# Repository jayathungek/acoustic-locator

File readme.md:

Table of Contents
=================

   * [acoustic-locator](#acoustic-locator)
      * [Hardware setup](#hardware-setup)
        * [The Microphone Circuit](#the-microphone-circuit)
        * [The Humidity/Temperature Sensor](#the-humiditytemperature-sensor)
        * [The Laser LED circuit](#the-laser-led-circuit)
        * [The Servo Circuit](#the-servo-circuit)
        * [Mechanical Design](#mechanical-design)
      * [Prerequisites](#prerequisites)
      * [Installation](#installation)
      * [How to use](#how-to-use)
      
# acoustic-locator

## Hardware setup

The acoustic locator hardware consists of two basic modules. The first module is the microphone module build on a PCB board that enables the placement of three MEMS microphones. The second module is the positioning module which consists basically of two servo motors, one being responsible for the horizontal movement of the mechanism and the other for the vertical. The front and back views of the acoustic locator are shown in figure 1. The sound source direction detection is achieved with the use of three microphones forming an equilateral triangle. The three holes at the edges of the acoustic locator identified on the front view are the openings for the three microphones. The opening in the middle of the acoustic locator, shown in the front view is the opening for the laser diode. The back view shows the positioning mechanism with the two servo motors.

                            Figure 1
                            
 The PCB board for the microphones is shown in figure 2. An IDC connector is used to connect the board with the Raspberry Pi board. The microphones used are Integrated Inter-IC Sound Bus (I2S) compatible digital MEMS microphones. I2S is a serial bus standard/protocol that enable the interface of one or two microphones on a microcontroller through a serial connection. Since the acoustic locator uses three microphones, a multiplexer is used to enable the connection of the microphones on the I2S bus. 

The microphones board also contains the circuit for the humidity/temperature sensor. The reason for using this sensor is because the speed of sound can vary with the temperature and the humidity. If the acoustic locator is used in normal room conditions then there is no need for the temperature/humidity sensor. If the acoustic locator is going to be used in places with extreme temperatures or humidity then the values of the temperature and humidity can be used to calculate the speed of sound and adjust the operation of the acoustic locator accordingly. 

The third module on the microphones PCB board is a laser LED circuit consisting of a LED driver and the laser LED. The laser LED is used for testing purposes, in order to identify the direction at which the acoustic locator is pointing to. On the final product, the laser LED can be replaced by a web camera, so that the camera will point to the person speaking, as explained in the introduction of this report.

                            Figure 2
                            
### The Microphone Circuit

The microphones used by the acoustic locator are the ICS-43432 digital I2S microphones from InvenSence. The ICS-43432 microphone includes all the required circuitry so that it can be interfaced directly with a microcontroller or a DSP, without the use of an audio codec. As shown in figure 3 the ICS-43432 contains in the same package the MEMS sensor with the signal conditioning circuit, the A/D converter, the anti-aliasing filter and a 24-bit I2S interface. The data sheet, handling information and application notes for the ICS-43432 microphone can be found [here]( https://www.invensense.com/products/digital/ics-43432/).

The ‘Config’ input is used in cases where it is required to modify the internal registers of the device. For normal operation, the ‘Config’ signal must be connected to the ground.  The ‘Left/Right’ (LR) channel select signal is used to specify to which one of the two I2S channels is the microphone connected to. If the L/R pin is connected to the ground (or set to Low), the microphone outputs its signal to the left channel of the I2C frame. If the L/R pin is connected to the supply voltage (or set to High), the microphone outputs its signal to the right channel of the I2C frame.

The I2C signals are the ‘SCK’ (Serial Data Clock for the I2S interface) input signal, the ‘SD’ (Serial Data Output for the I2S interface) signal and the ‘WS’ (Serial Data Word Select for the I2S interface) input signal. If the ‘WS’ signal is set Low, the left microphone sends its data on the ‘SD’ signal, otherwise the right microphone sends its data. The ‘SD’ line must be pull down to the ground using a 100K resistor. A typical circuit with two microphones connected to a DSP or a microcontroller is shown in figure 4.

                              Figure 3

                              Figure 4
                              
The circuit diagram of the acoustic locator microphone board is shown in figure 5. Because the acoustic locator uses three microphones and the I2S interface supports only two, a demultiplexer is used to allow two microphone to share the same I2S channel. The demultiplexer used is the TS3A24159 dual 2-channel SPDT bidirectional analogue switch. As shown in the circuit diagram, the select input (In1) of the analogue switch is connected to the GPIO9 signal of the Raspberry Pi, while the Com input is connected to the WS signal (signal GPIO19).

Setting the In1 pin to low, the WS signal is switched to the WS signal of the Mic1 microphone, thus reading the data from Mic1.  Setting the In1 pin to high, the WS signal is switched to the WS signal of the Mic2 microphone, thus reading the data from Mic2. Since the LR inputs for Mic1 and Mic2 are connected to the supply voltage, both microphones are treated as Right channel microphones. The LS signal of microphone Mic3 is connected to the ground, therefore, this microphone is treated as the Left channel microphone.

                              Figure 5

### The Humidity/Temperature Sensor

The Humidity/Temperature Sensor used by the acoustic locator is the HIH6030-021-001 digital I2C humidity/temperature from Honeywell. This device combines a humidity and a temperature sensor in the same package. The data sheet, handling information and application notes for the HIH6030-021-001 digital I2C humidity/temperature can be found [here](https://sensing.honeywell.com/HIH6030-021-001-humidity-sensors). 

The pinout with the typical application circuit diagram, given in the device datasheet is shown in figure 13.The same circuit is used  by the acoustic locator as shown in the circuit diagram in figure 5.The SCL pin is connected to the I2C clock, while the SDA pin is connected to the I2C data line. Both the SCL and the SDA pins must be pulled up with a 2.2K resistor each. The supply pin must be decoupled with a 0.1µF capacitor, while the Vcore pin must be connected to the ground through a 0.22µF capacitor. The AL_L (Alarm Low) and the AL_H (Alarm High) pins are used in the case an external device such as a relay or a LED are needed to be controlled directly by the sensor.

                                Figure 6
                                                           
### The Laser LED circuit

The laser LED circuit, shown in figure 7, consists of the laser diode, MOSFET transistor driver and resistor. The transistor driver is used because the Raspberry Pi cannot provide the amount of current required to operate the laser LED. The resistor is used to limit the current through the laser to the value lower than the maximum LED current. The operation of the laser is achieved by controlling the state of the GPIO6 of the Raspberry Pi.

                                Figure 7
                                
### The Servo Circuit

The movement of the positioning mechanism is achieved by the use of two servo motors. These motors are connected by the Raspberry Pi, through a board that is attached on the Raspberry Pi as a shield shown in figure 8. This shield also provides a connection from the Raspberry Pi to the microphones board through an IDC connector and a ribbon cable.The circuit diagram for the connection of the two servo motors to the Raspberry Pi is shown in figure 9. The speed and direction of rotation of the servo motors is achieved through the PWM signals obtained from the GPIO12 and the GPIO13 signals of the Raspberry Pi.

                                Figure 8

                                Figure 9
                                
### Mechanical Design

The mechanical design consists of the direction mechanism. This design features three parts: (a) the base, (b) a gimbal and (c) the head.

The base serves two functions: it supports the device as well as houses the Raspberry Pi, along with the locator interface board. The design allows the Raspberry Pi to be connected to a PC/laptop without opening the base.
The pan/tilt gimbal aids the movement of the device. It is capable of 180° rotation around the vertical axis as well as 100° up and down. The gimbal is mounts on top of the base as well as holding the head.

The head – a 3D printed part – clicks in place on top of the gimbal. The part is designed to secure the microphones in their respective places. The PCB just slides intro the head, thus no screws are required to hold the electronics on the gimbal.

## Prerequisites
The following steps are needed to configure the raspberry pi for I2S microphone support:

1. Enable I2S communication:- 
  ```
  $ sudo nano /boot/config.txt
  ```
  1.1 Navigate the file and uncomment the the line that contains `#dtparam=i2s=on`. 
  
2. Add the reference for the chip on the Raspberry Pi 3 that handles the I2S into the modules file:- 
  ```
  $ sudo nano  /etc/modules
  ``` 
  2.1 Add the line `snd-bcm2835` to this file.
  
3. Reboot:- 
  ```
  $ sudo reboot
  ```
  
4. Run this command and verify that it outputs `snd_soc_bcm2835_i2s`:-
  ```
  $ lsmod | grep snd
  ```
  
5. Install dependancies and set permissions:- 
  ```
  $ sudo apt-get -y install bc libncurses5-dev
  $ sudo wget https://raw.githubusercontent.com/notro/rpi-source/master/rpi-source -O /usr/bin/rpi-source`
  $ sudo chmod +x /usr/bin/rpi-source
  ```
6. Update `rpi-source` and run:-
  ```
  $ /usr/bin/rpi-source -q --tag-update`
  $ rpi-source
  ```
  
7. Mount the developent system debugger:-
  ```$ sudo mount -t debugfs debugs /sys/kernel/debug```
  
8. Check for the presence of the 3f203000.i2s module:-
  ```$ sudo cat /sys/kernel/debug/asoc/platforms```
  
9. Download Paul Creaser's I2S audio module, navigate to it and build it:-
  ```
  $ git clone https://github.com/PaulCreaser/rpi-i2s-audio
  $ cd rpi-i2s-audio
  $ make -C /lib/modules/$(uname -r )/build M=$(pwd) modules
  ```
  
10. Insert this module and verify its presence:-
  ```
  $ sudo insmod my_loader.ko
  $ lsmod | grep my_loader
  $ dmesg | tail
  ```
  
11. To load the module every time the pi is booted up:-
  ```
  $ sudo cp my_loader.ko /lib/modules/$(uname -r)
  $ echo 'my_loader' | sudo tee --append /etc/modules > /dev/null
  $ sudo depmod -a
  $ sudo modprobe my_loader
  ```

## Installation
1. Clone this repository: `$ git clone git@github.com:jayathungek/acoustic-locator.git`
2. Navigate to the main directory: `$ cd acoustic-locator`
3. Run tests: `$ make runtests`. All the tests should pass.
4. Build: `$ make`

A binary called `locator` is generated in the current working directory. Running this with `$ sudo ./locator` will start the main loop of the program and the gimbals will move in response to loud noises. Alternatively, f you wish to run `locator` on boot, edit `/etc/rc.local` so that it contains the path to the binary:
   ```
   #!/bin/sh -e
   #
   # rc.local
   #
   # This script is executed at the end of each multiuser runlevel.
   # Make sure that the script will "exit 0" on success or any other
   # value on error. 
   #
   # In order to enable or disable this script just change the execution
   # bits.
   #
   # By default this script does nothing.

   sudo /home/pi/acoustic-locator/locator &

   exit 0
   ```

## How to use
The raspberry pi is powered by a 5V micro usb cable and is perfectly capable of driving the servo motors from its 5V pins. Assuming all the steps above have been followed, simply plugging in the device to any 5V DC supply will start the location program.

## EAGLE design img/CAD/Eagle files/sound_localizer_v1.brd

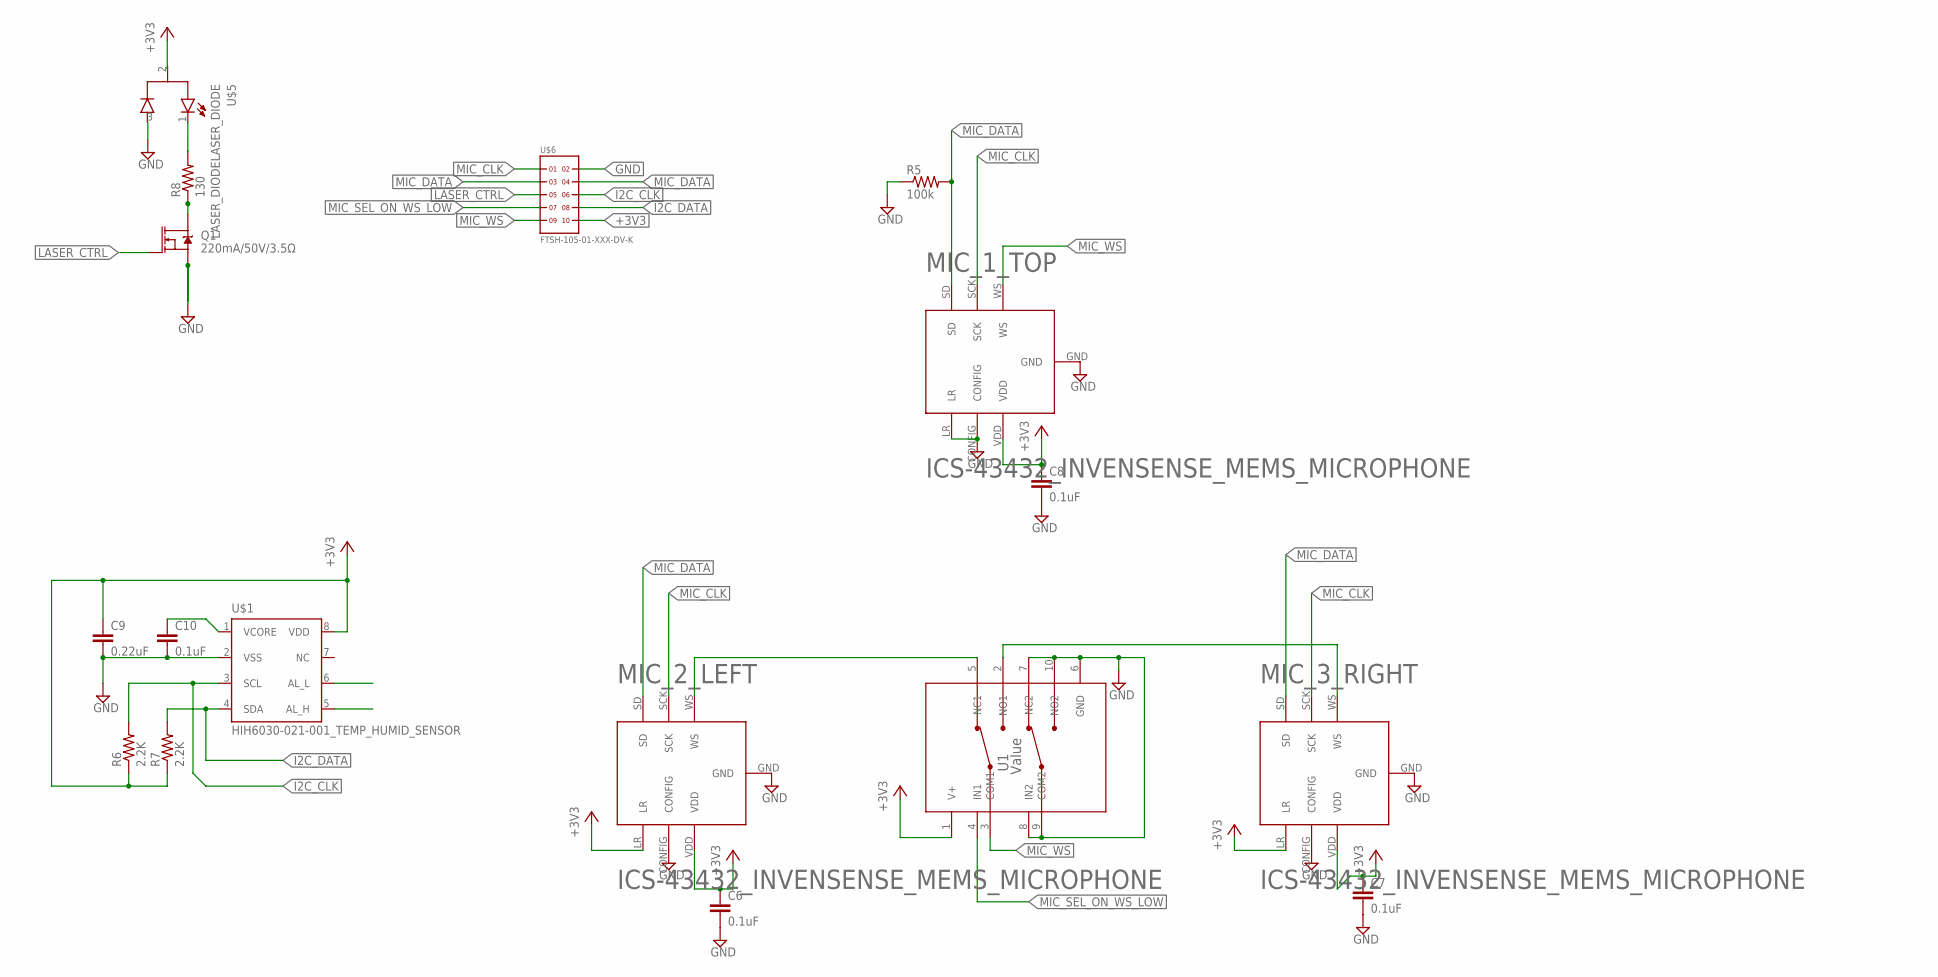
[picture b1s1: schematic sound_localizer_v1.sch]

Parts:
C6, C7, C8, C10: 0.1uF; C0805K
C9: 0.22uF; C0805K
MIC_1_TOP, MIC_2_LEFT, MIC_3_RIGHT: ICS-43432_INVENSENSE_MEMS_MICROPHONE; MEMS_MIC
Q1: 220mA/50V/3.5Ω; SOT23-3
R5: 100k; M0805
R6, R7: 2.2K; M0805
R8: 130; M0805
U1: Value; DGS0010A_N
U$1: HIH6030-021-001_TEMP_HUMID_SENSOR; SOIC8
U$5: LASER_DIODELASER_DIODE; TO46-LX
U$6: FTSH-105-01-XXX-DV-K

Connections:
+3V3: C6.1, C7.1, C8.1, C9.1, MIC_1_TOP.VDD, MIC_2_LEFT.LR, MIC_2_LEFT.VDD, MIC_3_RIGHT.LR, MIC_3_RIGHT.VDD, R6.1, R7.1, U1.1 (V+), U$1.8 (VDD), U$5.2, U$6.10
GND: C6.2, C7.2, C8.2, C9.2, C10.2, MIC_1_TOP.CONFIG, MIC_1_TOP.GND, MIC_1_TOP.LR, MIC_2_LEFT.CONFIG, MIC_2_LEFT.GND, MIC_3_RIGHT.CONFIG, MIC_3_RIGHT.GND, Q1.2 (S), R5.1, U1.6 (GND), U1.7 (NC2), U1.8 (IN2), U1.9 (COM2), U1.10 (NO2), U$1.2 (VSS), U$6.2
I2C_CLK: R6.2, U$1.3 (SCL), U$6.6
I2C_DATA: R7.2, U$1.4 (SDA), U$6.8
LASER_CTRL: Q1.1 (G), U$6.5
LED_CATHODE: R8.2, U$5.1
MIC_CLK: MIC_1_TOP.SCK, MIC_2_LEFT.SCK, MIC_3_RIGHT.SCK, U$6.1
MIC_DATA: MIC_1_TOP.SD, MIC_2_LEFT.SD, MIC_3_RIGHT.SD, R5.2, U$6.3, U$6.4
MIC_SEL_ON_WS_LOW: U1.4 (IN1), U$6.7
MIC_WS: MIC_1_TOP.WS, U1.3 (COM1), U$6.9
unnamed: MIC_2_LEFT.WS, U1.5 (NC1)
unnamed: MIC_3_RIGHT.WS, U1.2 (NO1)
unnamed: C10.1, U$1.1 (VCORE)
unnamed: Q1.3 (D), R8.1
NC: U$1.6 (AL_L)
P$1: U$5.3

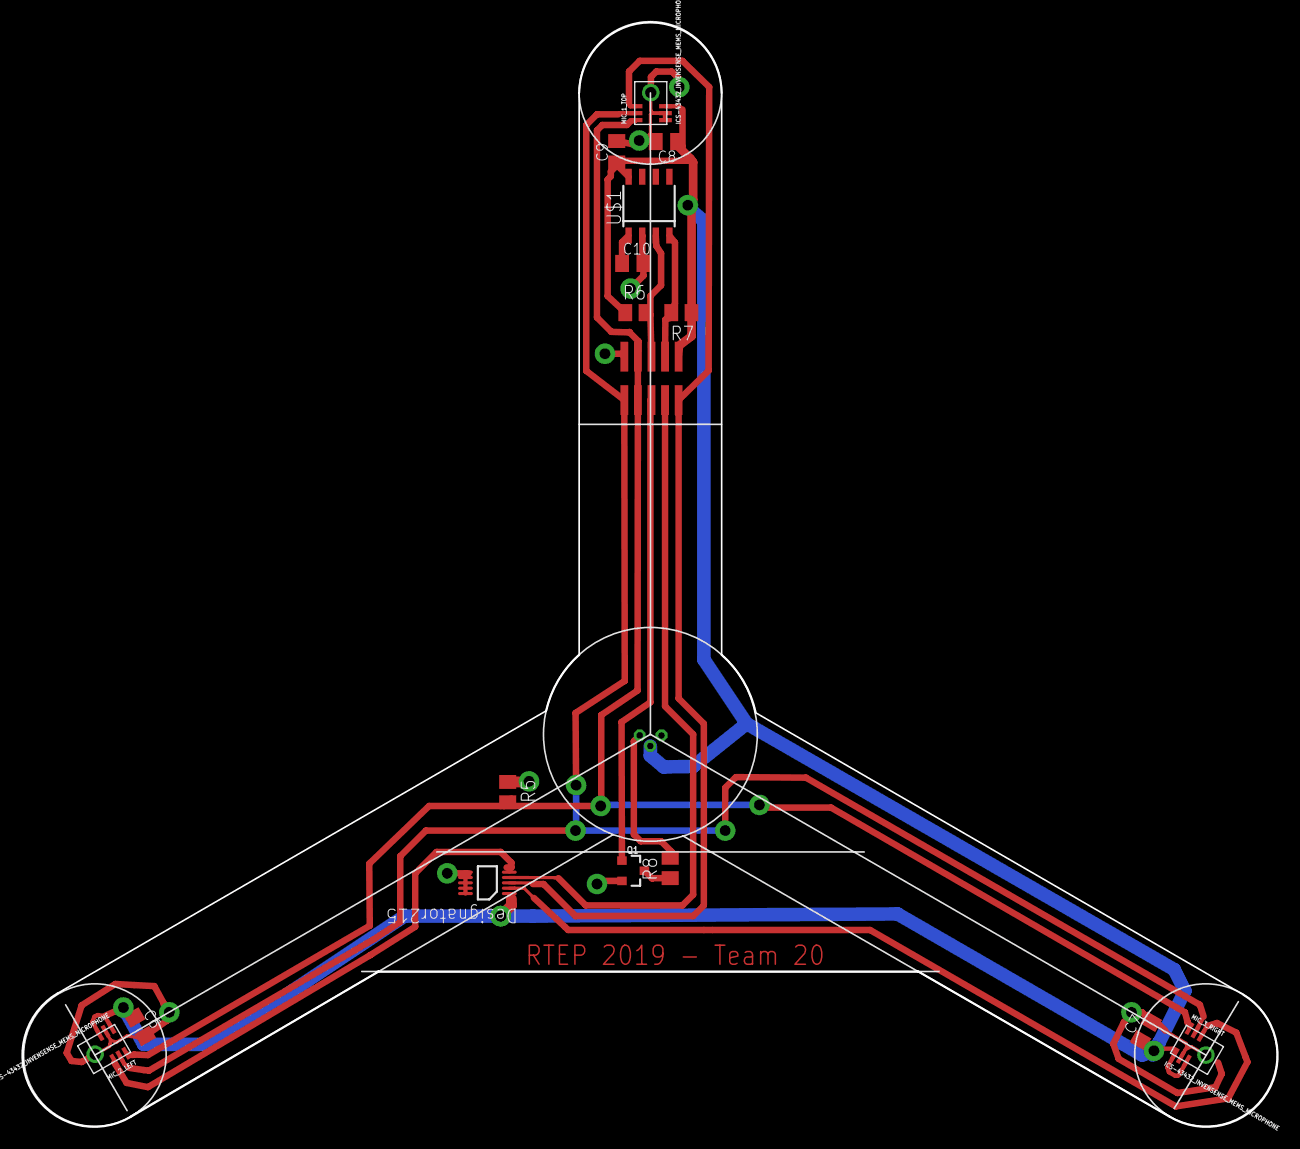
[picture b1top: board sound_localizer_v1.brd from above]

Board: 2 copper layers, 117.4 x 103.3 mm, 17 parts (1 on the bottom side), 14 nets.

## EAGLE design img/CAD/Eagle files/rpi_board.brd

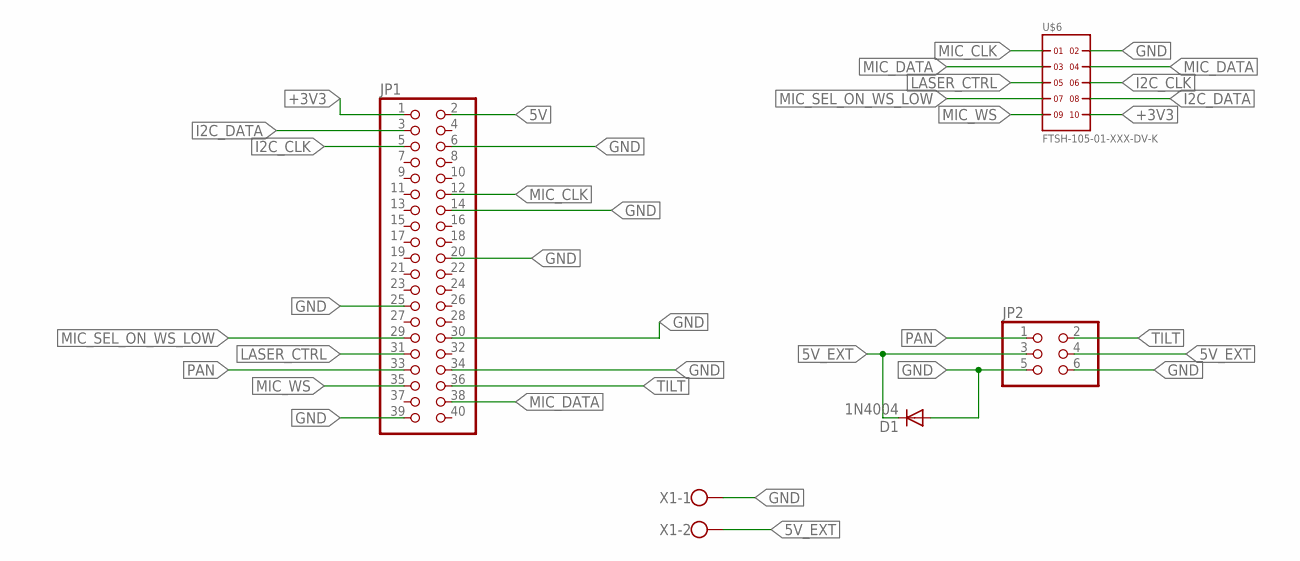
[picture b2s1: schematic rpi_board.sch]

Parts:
D1: 1N4004; DO41-10
JP1: PINHD-2X20; 2X20
JP2: PINHD-2X3; 2X03
U$6: FTSH-105-01-XXX-DV-K
X1: W237-102

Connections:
5V: JP1.2
5V_EXT: D1.C, JP2.3, JP2.4, X1.2
+3V3: JP1.1, U$6.10
GND: D1.A, JP1.6, JP1.14, JP1.20, JP1.25, JP1.30, JP1.34, JP1.39, JP2.5, JP2.6, U$6.2, X1.1
I2C_CLK: JP1.5, U$6.6
I2C_DATA: JP1.3, U$6.8
LASER_CTRL: JP1.31, U$6.5
MIC_CLK: JP1.12, U$6.1
MIC_DATA: JP1.38, U$6.3, U$6.4
MIC_SEL_ON_WS_LOW: JP1.29, U$6.7
MIC_WS: JP1.35, U$6.9
PAN: JP1.33, JP2.1
TILT: JP1.36, JP2.2

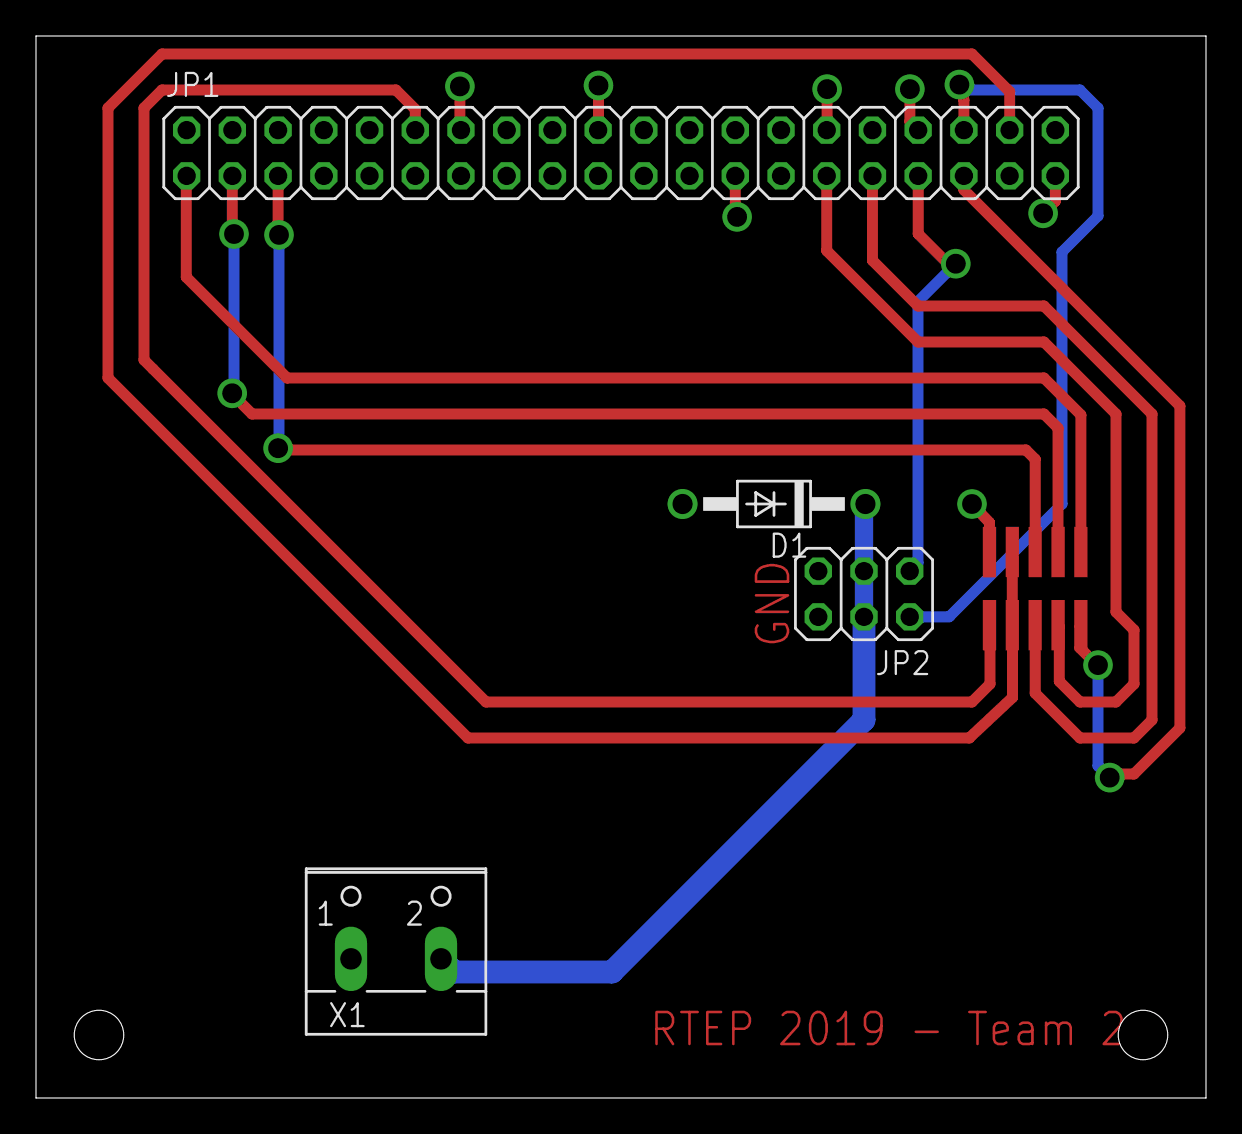
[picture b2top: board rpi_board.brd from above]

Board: 2 copper layers, 65.0 x 59.0 mm, 5 parts (0 on the bottom side), 12 nets.

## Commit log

2019-01-21 Added readme
2019-01-21 Added gitignore
2019-01-29 added CAD images
2019-02-07 updated gitignore
2019-02-07 Implements test code that verifies SPI communication between MCP3208 ADC and RPi
2019-02-07 Add comments
2019-02-14 established communication between i2s temp sensor and Rpi
2019-02-21 added code to test gpio clocks
2019-02-25 created rudimentary software multiplexer
2019-02-26 make multiplexer neater
2019-02-26 general cleanup of variable names
2019-02-26 added makefile
2019-02-26 abstracted mux threads away into separate functions
2019-03-04 wrote wrapper code to access hardware gpio functions
2019-04-01 add i2stest code
2019-04-09 added sample code
2019-04-10 graphing with QT added
2019-04-10 successfully able to record clean audio at 16bit depth
2019-04-10 can set device and duration from cmd
2019-04-10 plot 2 channel audio from a csv
2019-04-11 can parse 16bit LE
2019-04-11 peak finder added
2019-04-11 normalization functionality added
2019-04-11 filter main stereo buffer into 3 mono buffer
2019-04-12 add extra buffer for second readin
2019-04-12 added array copy function
2019-04-12 functions for servos
2019-04-12 minimal unit testing framework
2019-04-12 add gitignore
2019-04-12 reorganise files for merge
2019-04-12 locator main added
2019-04-12 update gitignore
2019-04-12 added csv files
2019-04-12 bugs fixed
2019-04-12 remove csv code
2019-04-13 main function updated
2019-04-13 copied in updated main code
2019-04-13 readmics() functional
2019-04-13 made code a bit more readable
2019-04-13 fix formatting
2019-04-13 added angle finder
2019-04-14 added part of the servo code
2019-04-14 locator functionality added
2019-04-14 plotting 3 mic data
2019-04-14 cad added
2019-04-14 implement updatePosition() fuction
2019-04-14 fixed some isues with servo control
2019-04-14 add debugging code
2019-04-14 add more debugging code
2019-04-14 cleanup variables
2019-04-14 add laser control
2019-04-14 fixed peak detection bug
2019-04-14 left rigth delay calculated
2019-04-14 bugs in calcDelay() function
2019-04-14 direction finding roughly works
2019-04-14 cleanup directory
2019-04-15 added formatted comments for doxygen
2019-04-15 add more doxygen comments
2019-04-15 add doxygen html and tex files
2019-04-15 moved minunit.h to test folder
2019-04-15 updated doxygen documentation
2019-04-15 add new minunit.h
2019-04-15 add more skeleton test units
2019-04-15 remove CMakeLists.txt
2019-04-15 change build instructions
2019-04-15 make functions more modular
2019-04-15 move servo specifc code
2019-04-15 utility functions in separate file
2019-04-15 remove temp sensor code
2019-04-15 csv files
2019-04-15 update doxygen documentation
2019-04-15 Fix documentation comments
2019-04-15 Update readme with link to doxygen documentation
2019-04-15 That was silly.. removed link
2019-04-15 Move makefile
2019-04-15 add Makefile
2019-04-15 eagle schematic files added
2019-04-15 eagle board files added
2019-04-15 change build rules to allow for testing
2019-04-15 add unit test for servo motors
2019-04-15 remove debug statements
2019-04-15 fix endianness bug in convertValue()
2019-04-15 add mockup function for turnMotorTo() in order to unit test
2019-04-15 add latex images
2019-04-16 add graph image
2019-04-16 Update readme.md
    Added latex style equations , and a graph to help explain the locator function
2019-04-16 Update readme.md
    fixed mistake
2019-04-16 Update readme.md
    fix typo
2019-04-16 remove object files
2019-04-16 generate doxygen docs
2019-04-16 Update readme.md
    Add clone/build instructions
2019-04-16 Update readme.md
    Add Usage instructions
2019-04-16 Update readme.md
    Added dependancy instructions
2019-04-16 Update readme.md
    remove heading
2019-04-16 add licencing information
2019-04-16 update updatePosition() function
2019-04-16 Update readme.md
    move some sections to the wiki
2019-04-17 change main for loop into while loop

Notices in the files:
parts and their libraries:
SparkFun-DiscreteSemi: Licensing: Creative Commons ShareAlike 4.0 International - https://creativecommons.org/licenses/by-sa/4.0
